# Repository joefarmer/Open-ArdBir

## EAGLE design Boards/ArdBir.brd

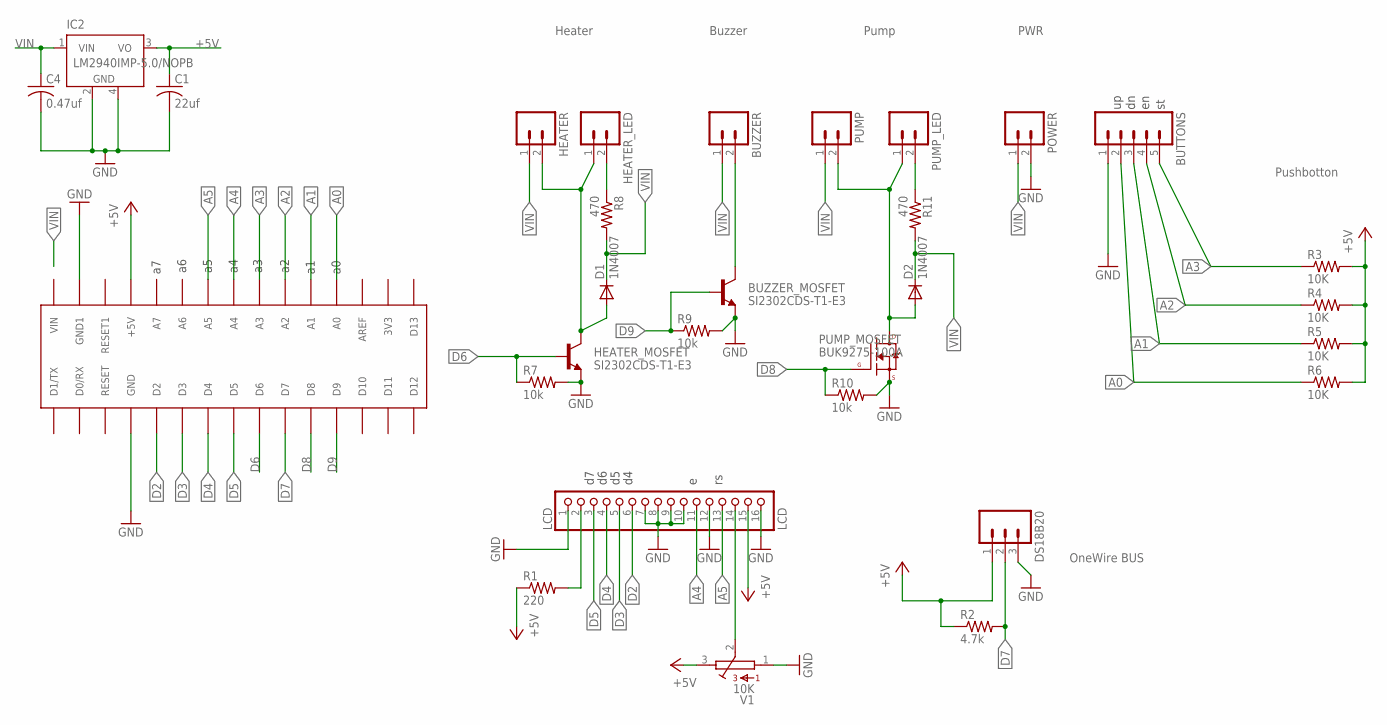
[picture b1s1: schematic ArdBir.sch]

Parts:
BUTTONS: M05LOCK; 1X05_LOCK
BUZZER: M02LOCK; 1X02_LOCK
BUZZER_MOSFET: SI2302CDS-T1-E3; SOT23
C1: 22uf; C0805
C4: 0.47uf; C0805
D1: 1N4007; SOD-123_MINI-SMA
D2: 1N4007; SMB-DIODE
DS18B20: M03LONGPADS; 1X03_LONGPADS
HEATER: M023.5MM-NO_SILK; SCREWTERMINAL-3.5MM-2-NS
HEATER_LED: M02LOCK; 1X02_LOCK
HEATER_MOSFET: SI2302CDS-T1-E3; SOT23
IC2: LM2940IMP-5.0/NOPB; SOT223
LCD: LCD; 1X16
POWER: M023.5MM-NO_SILK; SCREWTERMINAL-3.5MM-2-NS
PUMP: M023.5MM-NO_SILK; SCREWTERMINAL-3.5MM-2-NS
PUMP_LED: M02LOCK; 1X02_LOCK
PUMP_MOSFET: BUK9275-100A; DPAK
R1: 220; 0805
R2: 4.7k; 0805
R3, R4, R5, R6: 10K; 0805
R7, R9, R10: 10k; R0805
R8, R11: 470; 0805
U$1: ARDUINONANO; PDIP-32
V1: 10K; CA9V

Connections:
+5V: C1.1, DS18B20.1, IC2.3 (VO), LCD.15, R1.1, R2.1, R3.2, R4.2, R5.2, R6.2, U$1.+5V, V1.3
A0: BUTTONS.2, R6.1, U$1.A0
A1: BUTTONS.3, R5.1, U$1.A1
A2: BUTTONS.4, R4.1, U$1.A2
A3: BUTTONS.5, R3.1, U$1.A3
A4: LCD.11, U$1.A4
A5: LCD.13, U$1.A5
BUZZER_OUT: BUZZER.2, BUZZER_MOSFET.3 (C)
D2: LCD.6, U$1.D2
D3: LCD.5, U$1.D3
D4: LCD.4, U$1.D4
D5: LCD.3, U$1.D5
D6: HEATER_MOSFET.1 (B), R7.1, U$1.D6
D7: DS18B20.2, R2.2, U$1.D7
D8: PUMP_MOSFET.1 (G), R10.1, U$1.D8
D9: BUZZER_MOSFET.1 (B), R9.1, U$1.D9
GND: BUTTONS.1, BUZZER_MOSFET.2 (E), C1.2, C4.2, DS18B20.3, HEATER_MOSFET.2 (E), IC2.2 (GND), IC2.4 (GND), LCD.1, LCD.7, LCD.8, LCD.9, LCD.10, LCD.12, LCD.16, POWER.2, PUMP_MOSFET.3 (S), R7.2, R9.2, R10.2, U$1.GND, U$1.GND1, V1.1
HEATER_OUT: D1.A, HEATER.2, HEATER_LED.1, HEATER_MOSFET.3 (C)
unnamed: PUMP_LED.2, R11.1
unnamed: LCD.14, V1.2
unnamed: HEATER_LED.2, R8.1
unnamed: LCD.2, R1.2
PUMP_OUT: D2.A, PUMP.2, PUMP_LED.1, PUMP_MOSFET.4 (D)
VIN: BUZZER.1, C4.1, D1.C, D2.C, HEATER.1, IC2.1 (VIN), POWER.1, PUMP.1, R8.2, R11.2

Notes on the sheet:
OneWire BUS
Pushbotton
Heater
Buzzer
Pump
PWR

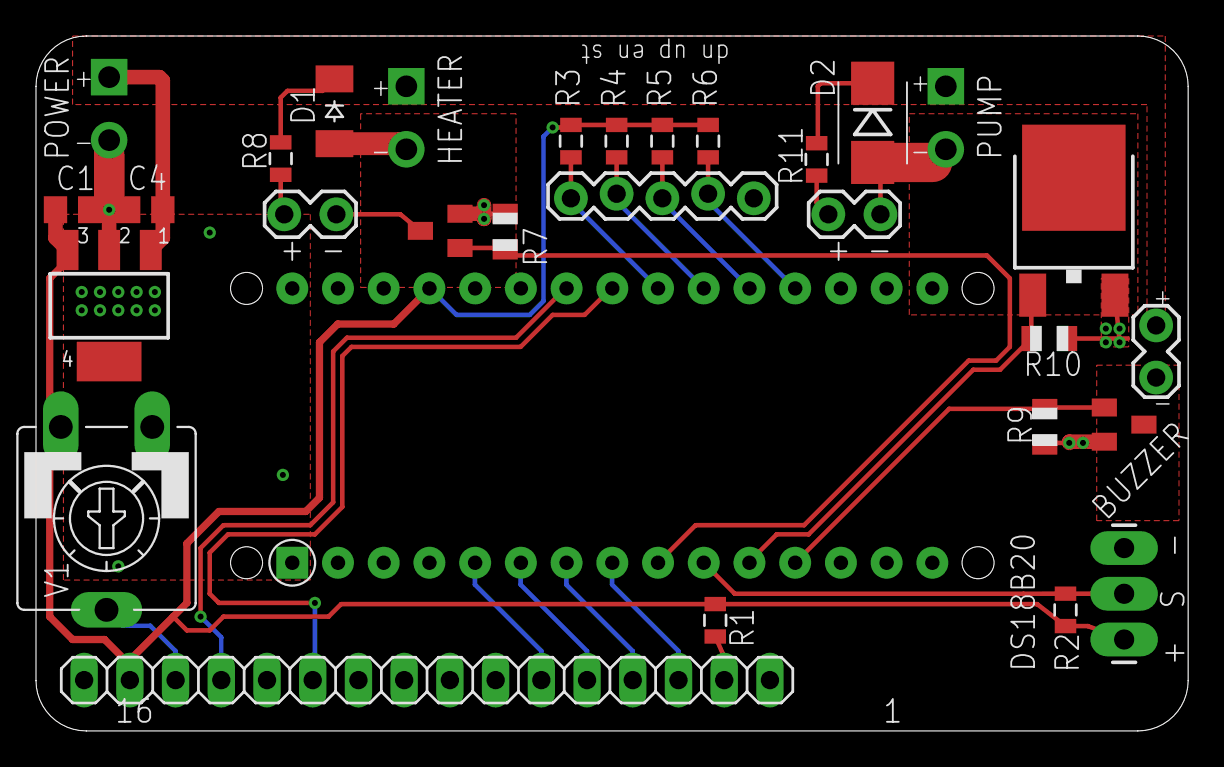
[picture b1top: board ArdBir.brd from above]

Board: 2 copper layers, 64.0 x 38.6 mm, 30 parts (0 on the bottom side), 24 nets.

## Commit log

2015-10-30 Initial commit for my nano ArdBir
2015-10-30 my nano config
2015-10-30 Shrink credits so it would compile in less than 32k
2015-10-30 Added part numbers for MOSFETs
2017-06-13 stripped for form

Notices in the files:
parts and their libraries:
SparkFun: Licensing: CC v3.0 Share-Alike You are welcome to use this library for commercial purposes.
